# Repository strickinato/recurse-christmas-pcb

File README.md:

# RECURSE CHRISTMAS PCB!

# Parts

- [Battery Pack](https://www.digikey.com/product-detail/en/BAT-HLD-012-SMT-TR/BAT-HLD-012-SMTCT-ND/5361777/?itemSeq=277985829)
- [Capacitors](https://www.digikey.com/product-detail/en/UWX1C101MCL1GB/493-2105-1-ND/590080/?itemSeq=277987980)
- [10K Resistors](https://www.digikey.com/product-detail/en/CRCW201010K0FKEF/541-10.0KACCT-ND/1179197/?itemSeq=277986744)
- [220 Resistors](https://www.digikey.com/product-detail/en/CRCW2010220RFKEFHP/541-220PCT-ND/2222678/?itemSeq=277986721)
- [LEDs](https://www.digikey.com/product-detail/en/WP503GDT/754-1875-ND/3084146/?itemSeq=277987537)
- [Transistors](https://www.digikey.com/product-detail/en/MMBT3904-TP/MMBT3904TPMSCT-ND/717395/?itemSeq=277988763)

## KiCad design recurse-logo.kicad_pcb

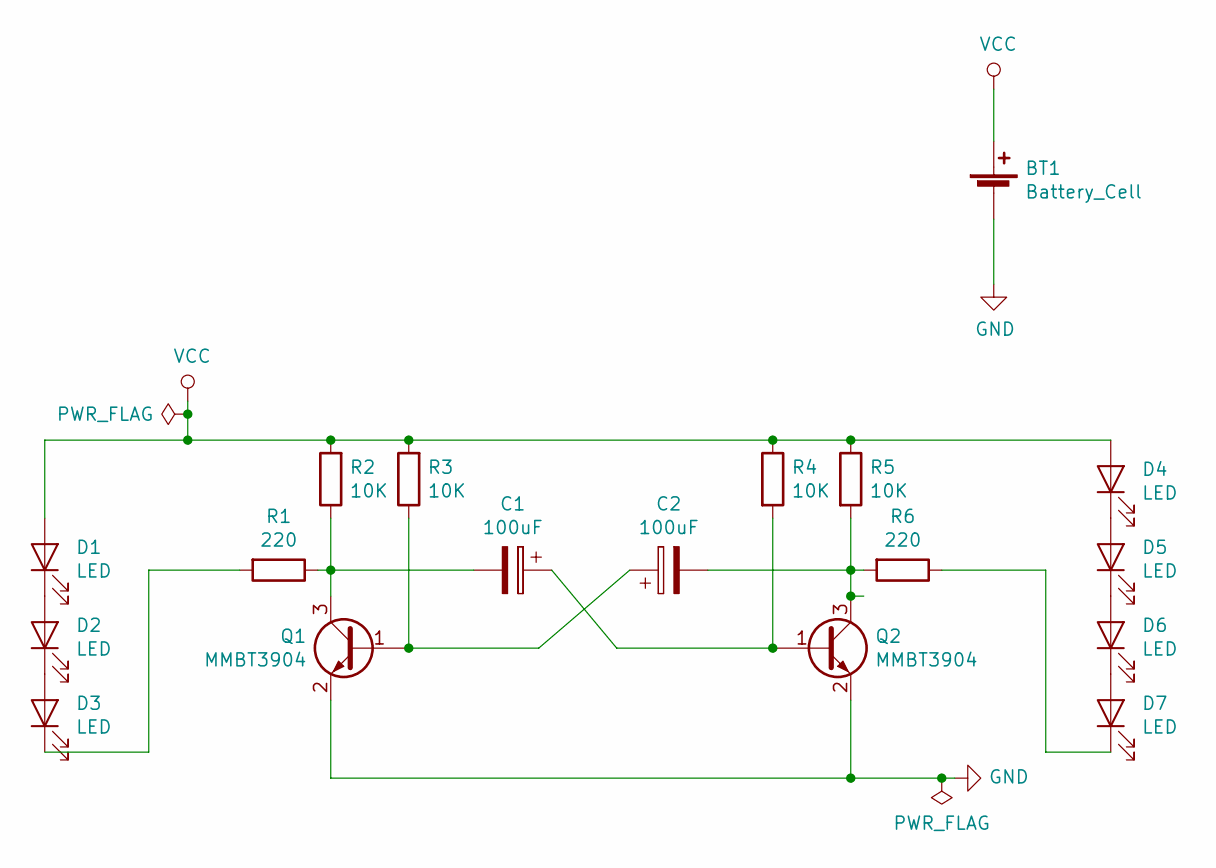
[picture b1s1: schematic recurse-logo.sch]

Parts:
BT1: Battery_Cell; BatteryHolder_LINX_BAT-HLD-012-SMT
C1, C2: 100uF; CP_Elec_6.3x5.4_Nichicon
D1, D2, D3, D4, D5, D6, D7: LED; LED_Rectangular_W5.0mm_H5.0mm-top-left
Q1, Q2: MMBT3904; SOT-23
R1, R6: 220; R_2010_5025Metric_Pad1.52x2.65mm_HandSolder
R2, R3, R4, R5: 10K; R_2010_5025Metric_Pad1.52x2.65mm_HandSolder

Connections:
GND: BT1.2 (-), Q1.2 (E), Q2.2 (E)
unnamed: C1.1, Q2.1 (B), R4.2
unnamed: C1.2, Q1.3 (C), R1.1, R2.1
unnamed: C2.1, Q1.1 (B), R3.1
unnamed: C2.2, Q2.3 (C), R5.2, R6.2
unnamed: D1.1 (K), D2.2 (A)
unnamed: D2.1 (K), D3.2 (A)
unnamed: D3.1 (K), R1.2
unnamed: D4.1 (K), D5.2 (A)
unnamed: D5.1 (K), D6.2 (A)
unnamed: D6.1 (K), D7.2 (A)
unnamed: D7.1 (K), R6.1
VCC: BT1.1 (+), D1.2 (A), D4.2 (A), R2.2, R3.2, R4.1, R5.1

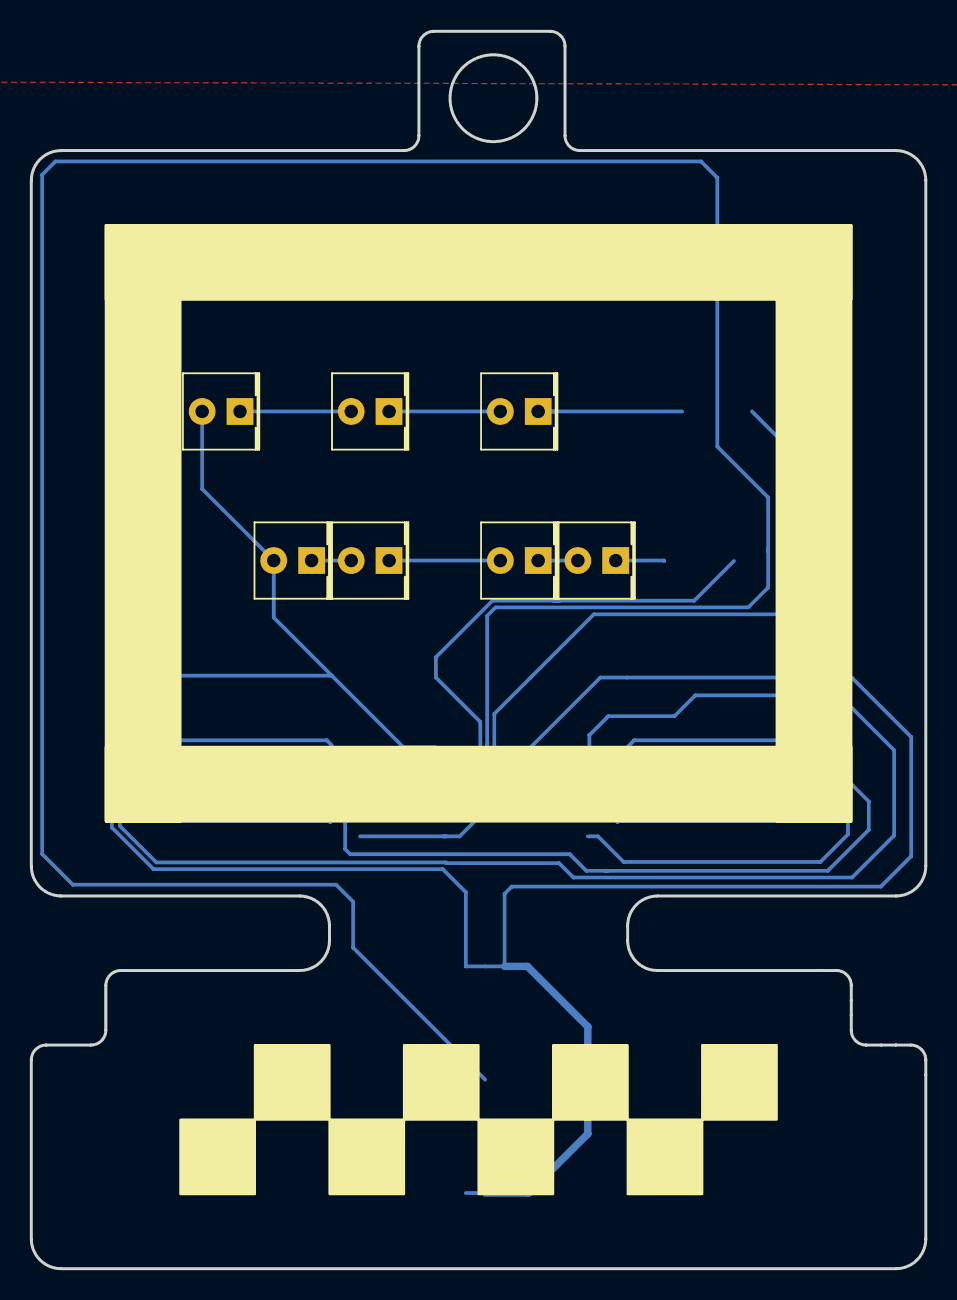
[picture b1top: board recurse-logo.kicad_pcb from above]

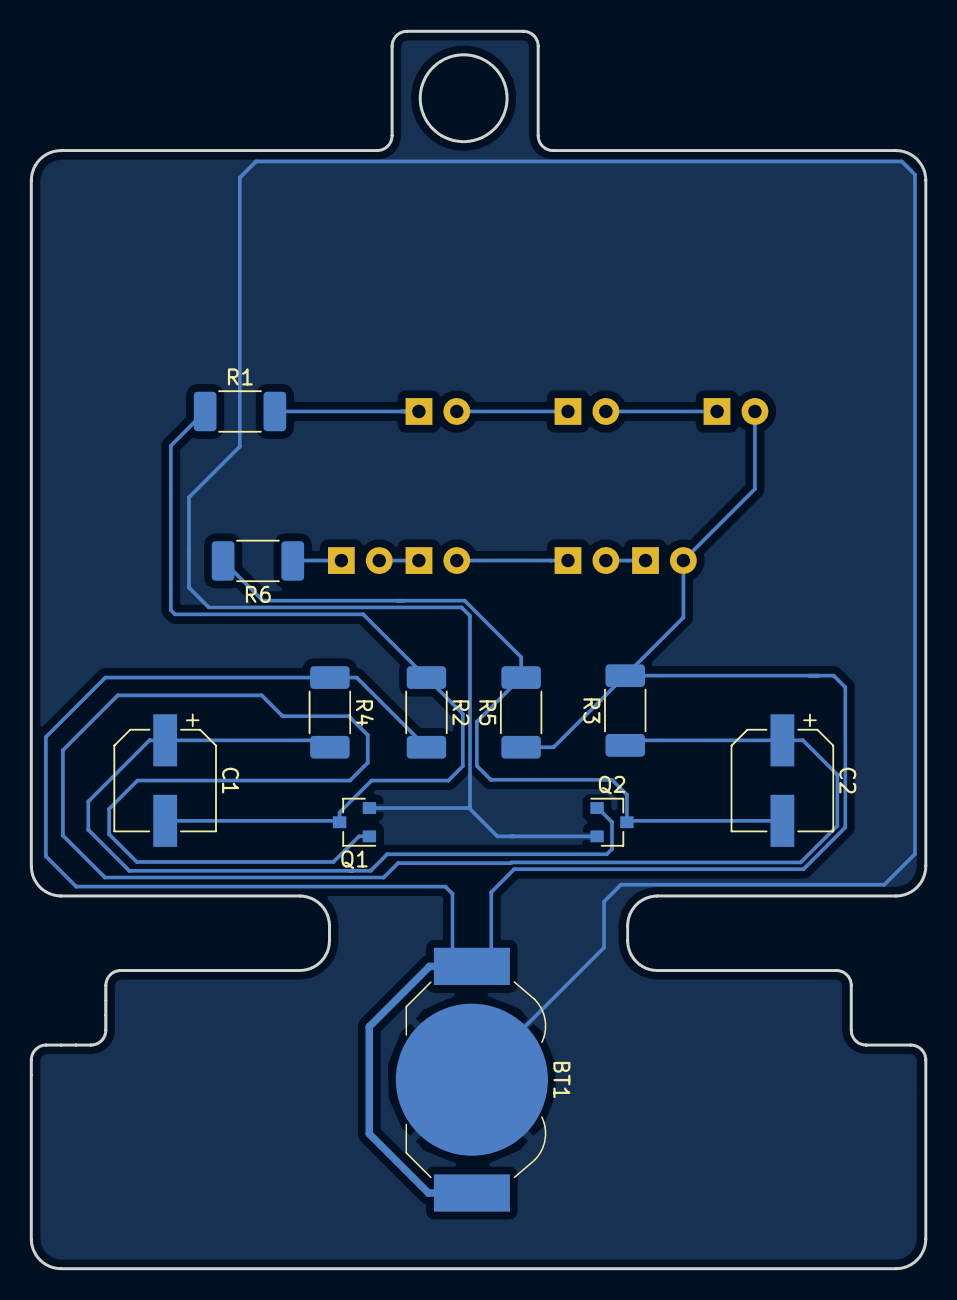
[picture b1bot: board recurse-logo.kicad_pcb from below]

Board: 2 copper layers, 60.0 x 83.0 mm, 18 parts (11 on the bottom side), 13 nets.

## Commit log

2018-11-19 all the files
2018-11-19 readme
2018-11-20 Updates and change to relative paths
2018-11-21 Wired it up! needs finishing touches
2018-11-21 Finished\!
2018-11-26 Add parts list
2018-11-26 clean readme
2018-11-26 remove old netlist so it's not confusing
2018-12-10 put LEDs in Parallel and get rid of the resistor\n also add the switch- but the assigned footprint isn't right
2018-12-19 add gif of blinky
